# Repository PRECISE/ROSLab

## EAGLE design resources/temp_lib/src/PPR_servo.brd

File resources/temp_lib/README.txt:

The Blocks folder contains a number of known-good schematics.  

Until a automated ulp is created, the instructions for making a new board are as follows:
1. Make a new schematic: File>New>Schematic
2. Import schematics: File>Import> find the schematic files you want included
	a) The only nets that should be connected by default (old name = new name) are V+, +5V, +3V3, GND or any other power rails or busses
3. Eagle does not carry over the sheet descriptions when imported.  Open the original files, right click on the sheet, select description, copy the html code.  
	a) Repeat the above steps in the new, combined schematic file, and paste the description in the appropriate location.
4. Read the instructions in the description.  It should instruct you to connect pins and anything else required for the circuit.  Look out for optional components.
	a) To connect pins, draw nets that are connected to the pins (they may already exist).  Do the same for all connected pins.  Then, rename all nets that should be connected to the same name.
5. Your schematic should be done at this point.  It is time to create a board from the schematic.
	a) To make a board from a schematic, File>Switch to Board> select yes if it asks to create from schematic.

Making new blocks:
1. Make a single sheet schematic
2. Add and connect symbols until you have a well contained part
3. For all nets that interact with outside schematic sheets, place a BLOCK_CONNECTOR symbol for each net and connect them
4. Name the nets according to the naming convention below:
	a) Serivce,Service#,1-to-many-symbol,Input-output-symbol,SuperService,SuperService#,AlternateFunction#/ ... (repeat for all possible services).PORT,PININ
	b) service (super service) options: GPIO (#), PWM (TIMER), PWM_N (TIMER), QEP (TIMER), TXRX (UART), SCK (SPI), MISO (SPI), MOSI (SPI), SCL (I2C), SDA (I2C), D+ (USB), D- (USB)

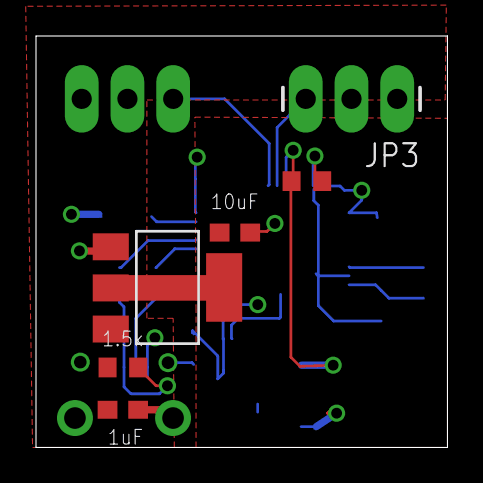
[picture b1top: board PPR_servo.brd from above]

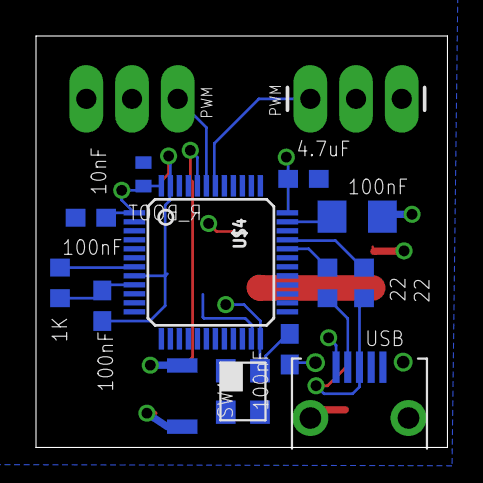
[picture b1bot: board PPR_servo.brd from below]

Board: 2 copper layers, 22.9 x 22.9 mm, 20 parts (14 on the bottom side), 13 nets.

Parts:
C6: 10 nF; C0402
CN2: USB-RECEPTABLE; FCI-10103594-0001LF
C_BYP_IN_1: 100nF; C1206
C_BYP_OUT_1: 10µF; C0603
C_MC_VDDA_1: 100nF; C0603
C_MC_VDD_1_1: 4.7uF; C0603
C_MC_VDD_2_1, C_MC_VDD_3_1: 100nF; C0603
C_USB_DC1: 1µF; C0603
JP1, JP3: 1X03_LONGPADS
R1, R3: 22; R0603
R2: 1.5k; R0603
R_BOOT_PU_1: 1k; R0603
R_NRST_PU_1: 1k; R0603
SW1: B3U
U$4: STM32F303CX; LQFP48
U$48: REG_SOT223LD1117XX; SOT-223
U$54: ASTX-H11

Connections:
3_3V,+,1: C6.1, C_BYP_OUT_1.1, C_MC_VDD_1_1.1, C_MC_VDD_2_1.1, C_MC_VDD_3_1.1, SW1.P$2, U$4.1, U$4.24, U$4.36, U$4.48, U$48.2, U$48.4, U$54.P$4
3_3V,+,I: C_MC_VDDA_1.1, R_NRST_PU_1.1, U$4.9
5V_USB,+,1: CN2.1, C_BYP_IN_1.1, C_USB_DC1.1, JP1.2, JP3.2, R2.1, U$48.3
16MHZ_CMOS,#,+,O,OSCILLATOR: U$4.5, U$54.P$3
BOOT0_1: R_BOOT_PU_1.1, SW1.P$1, U$4.44
D+,-,USB,1: R1.2, U$4.33
D+_IN_1: CN2.3, R1.1, R2.2
D-,-,USB,1: R3.2, U$4.32
D-_IN_1: CN2.2, R3.1
GND: C6.2, CN2.5, CN2.P$1, CN2.P$2, CN2.P$3, CN2.P$4, C_BYP_IN_1.2, C_BYP_OUT_1.2, C_MC_VDDA_1.2, C_MC_VDD_1_1.2, C_MC_VDD_2_1.2, C_MC_VDD_3_1.2, C_USB_DC1.2, JP1.1, JP3.1, R_BOOT_PU_1.2, U$4.8, U$4.23, U$4.35, U$4.47, U$48.1, U$54.P$2
NRST_1: R_NRST_PU_1.2, U$4.7
TIMER,PWM,-,1: JP1.3, U$4.42
TIMER,PWM,-,2: JP3.3, U$4.43

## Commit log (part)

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2014-02-26 Create gh-pages branch via GitHub
2014-02-26 Initial import from existing 'roslab' repo.
2014-02-26 Initial JavaFX project skeleton.
2014-02-26 Adding referenced libraries.
2014-03-10 Added base module set.
2014-03-10 Added loading of built-in modules from file.
2014-03-10 Removed unused include.
2014-03-10 Added release directory.
2014-03-10 Updated FXML file.
2014-03-12 Organized files into v1 release.
2014-03-12 Renamed version to v1.0.0.
2014-03-18 Added example entry to modules.xml.
2014-03-18 Added README: user documentation.
2014-03-18 New v1.0.0 archive with recent changes included.
2014-03-27 Renamed Channel class to Link.
2014-03-27 Adding new classes.
2014-03-27 Added new classes.
2014-03-27 Renamed these classes.
2014-03-27 Updated root type. Added application window title.
2014-03-27 Removed unused css file.
2014-03-27 Added TreeView.
2014-03-27 Updated constructors.
2014-04-08 Removed default status label text.
2014-04-08 Building data model classes.
2014-04-23 Added quad templates.
2014-05-13 Added JDOM and String Template libraries.
2014-05-13 Added ROS templates.
2014-05-13 Added Model Processor stub classes.
2014-05-16 Added new hardware model classes.
2014-05-16 Added getters/setters.
2014-05-16 Added HW Bot template.
2014-05-16 Updated HWBlockTypes.
2014-05-19 Added test for HardwareModelProcessor.
2014-05-19 Added getName() method to Endpoint interface.
2014-05-19 Changed Link name to be based on names of src and dest.
2014-05-19 Added getUILinksOfType() method to Configuration.
2014-05-19 Added string building for all HardwareModelProcessor methods.
2014-05-22 Python project files added due to use of Python in generated output files.
2014-05-22 Added main launch file for ROSLab FX.
2014-05-22 Changed str.concat to str +=
2014-05-22 Added fx:id for tab panes.
2014-05-22 Added FXML tags on tab panes.
2014-05-22 Added methods to Pin.
2014-05-22 Added constructors to PinService.
2014-05-22 Added more complete test configuration.
2014-05-22 Increased UINode size and changed color.
2014-05-22 Added CSS styling.
2014-05-23 Seems to have fixed scroll bars showing in ScrollPane.
2014-05-23 Added selection rectangle to ROSLabController.
2014-05-26 Removed PyDev from project.
2014-05-29 Added UIEndpoints to UINodes.
    Draggable with the UINode, too!
2014-06-05 Designing Dialog window for adding links.
2014-06-05 Adding support for drawing links in the UI.
2014-06-05 Adjusted node stroke colors.
2014-06-05 Added test nodes to other tab panes.
2014-07-21 Work on TreePane
2014-07-21 Updated project-specific Eclipse settings.
2014-07-21 Updated project-specific properties.
2014-07-22 Added ability to modify User Defined Node ports.
2014-07-31 Added getNodesOfClass method.
2014-07-31 Work on modifying ROSNodes for testing.
2014-09-11 Code formatting cleanup.
2014-09-11 Changed Node class to not use JavaFX properties (for now).
2014-09-11 Added addJoint method to HWBlock class.
2014-09-11 Added some basic getter/setter methods for main model classes.
2014-10-03 Added XStream library.
2014-10-06 Formatting update.
2014-10-06 Fixed Library tree loading.
2014-10-07 Added fxml for Functionality window.
2014-10-08 Updated formatting.
2014-10-14 Added JavaFX handles for tabs.
2014-10-14 Minor method name tweak.
2014-10-14 Added mouse event handling.
2014-10-14 Added UINode and UILink handling methods.
2014-10-14 Added SnakeYAML and Jython libraries to project.
2014-10-14 Added Mechanics Python-handling code from PPR branch.
2014-10-14 Changed field visibility to protected.
2014-10-20 Moved processor classes.
2014-10-27 Added unimplemented methods.
2014-10-27 Added scroll panes to right-hand-side accordion.
    Updated tab names slightly.
2014-10-27 Added ROSModelCompiler class from ROSLab 1.0
2014-10-27 Updated import.
2014-11-18 Added rosmsgs.
2014-11-18 Added null checks.
2014-11-18 Added another ROSPortType: Odometry.
2014-11-18 Added example ROS package.
2014-11-19 Switched to use StringTemplate 3.2.1.
2014-11-19 Renamed ROSModelCompiler.
2014-11-19 Updated ROS template files.
2014-11-19 Fixed whitespace in templates.
2014-11-19 Added new constructors for Circuit, Joint, HWBlock.
2014-11-19 Moved HardwareModelProcessorTest.
2014-11-19 Improved constructors.
2014-11-19 Added rate methods and publishers/subscribers methods.
2014-11-20 Added Platform class, a test class for the parser, and a test Platform YAML file.
2014-11-21 Added electronics schematics, moved mechanics and software libraries.
2014-11-21 Added ROSPortType class with static map of ROS message types.
2014-11-24 Finished Platform and PlatformParser.
2014-11-24 Commented out blocks to be updated later for version 2 data model.
2014-11-26 Cleanup.
2014-11-26 Added ROSTopic class.
2014-11-26 Updated author.
2014-12-09 Improved Link API.
2014-12-09 Added Platform feature.
2014-12-09 Added some helper functions.
2014-12-09 Added new dialog windows.
2014-12-16 Excluding a couple of unused classes.
2014-12-16 Deleted unused package-info classes.
2014-12-16 Added EagleSchematic class to handle interactions with EAGLE schematics.
2014-12-16 Added clone support to main model classes.
    Also, added electronics naming scheme parsing.
2014-12-17 Added NewNodeDialog and fixed other dialogs.
2014-12-17 Added name field to Library.
2014-12-17 Added contains() methods and getEndpoints() to Configuration class.
2014-12-17 Removed obsolete class.
2014-12-17 Added context menu support to tree.
2014-12-17 Switched Configuration back to using non-UI-specific classes.
2014-12-18 Added remove methods.
2014-12-18 Updated test to use non-UI classes.
2014-12-18 Added back non-UI getLinksOfType method.
2014-12-19 Reorganized UI package structures.
2014-12-19 Added getNodesOfType(clazz) method.
2014-12-20 Removed obsolete commented code.
2014-12-20 Added NewUserDefinedDialog.
2014-12-20 Made ROSMsgType class comparable.
2014-12-20 Removed obsolete and duplicate code from ROSLabTree class, added some removal methods.
2014-12-20 Improved Library & Configuration add and remove methods.
2014-12-20 Suppressing 'unchecked' warnings in PythonLibraryHelper.
2014-12-20 Updated fxbuild file, ignoring build directory for Git.
2014-12-20 Removed obsolete ROSLabTreeCell code, copied drag method to ROSLabTree class for future use.
2014-12-22 Added isInput and getAnnotations methods to Endpoints.
2014-12-22 Added FXML annotations to methods in ROSLabController.
    Added additional menu items to File menu.
2014-12-22 Added suppress warnings to dialog classes.
2014-12-23 Added TODO to ROSMsgType class.
2014-12-23 Improved topic info shown under Library nodes.
2014-12-23 Using Landshark platform library.
2015-01-13 Added switchLibrary method stub.
2015-01-13 Added loading of Electronics library.
    Includes methods for creating Circuit objects from EagleSchematics.
2015-01-13 Added eagle.dtd.
2015-01-14 Improved schematic parsing and creation of Pin objects.
2015-01-14 Fixed issues in schematic Net names.
2015-01-14 Added "simple" versions of two schematics.
2015-01-14 Swapped source and destination pins when attempting a connection.
2015-01-15 Fixed pin connection check, fixed missing assignedService assignment.
2015-01-24 Added getUIEndpoint method.
2015-01-24 Added ability to set UINode text, removed duplicated UINode text for Circuit blocks.
2015-01-24 Added check to ensure NewLinkDialog does not allow self-connections.
2015-01-25 Added check to ensure name field in NewNodeDialog is not empty.
2015-01-25 Added 'net' String field to Pin.
2015-03-02 Added Z3 library.
2015-03-02 Added pin matching algorithm.
2015-03-04 Added slf4j library.
2015-03-05 Added log4j.
2015-03-09 Added 'Delete' context menu item for the Links.
2015-03-11 Fixed typo in indexing.
2015-03-11 Added extra methods to Endpoint class.
2015-03-11 Added destroy() method to Link.
2015-03-12 Added link removal improvements, fixed indexing bugs in PinMatcher.
2015-03-12 Simplified Ok handler for NewLinkDialog.
2015-03-12 Fixed merge method for schematics, integrated pin-matching algorithm into Circuit connection process.
2015-03-13 Added more schematics.
2015-03-19 Simplified some schematic blocks.
2015-03-19 Attempting to display UILink in the background.
2015-03-19 Working towards fixing library and package merging issue.
2015-03-20 Fixed error in DeviceSet list iteration.
2015-03-22 Added random testing to PinMatcherTest.
2015-03-22 Trying to fix Z ordering of UILinks.
2015-03-22 Fixed Circuit so wire bundles are added to both Src and Dest when making a connection.
2015-03-22 Removing optional service from Radio pin.
2015-03-24 Added more checks to Pin connect().
2015-03-30 Adjusted pin matching algorithm to check for bus connections and to finish even when not fully connected
2015-03-30 Added parsing of destination set value on pin names
2015-03-31 Added new basic PinService constructor.
2015-03-31 Updated constructor to support bidirectionality.
2015-03-31 Fixed bug in bussable check in PinMatcher.
2015-03-31 Updated NewLinkDialog to disable Destination box when there aren't any valid destinations.
2015-03-31 Disabled superservice checking, improved I/O matching.
2015-04-06 Changed Standard Servo Header pin to Required.
2015-04-06 Added battery schematics.
2015-04-06 Fixed bug in pin name parsing, improved Wire naming.
2015-04-06 Updated driver schematic.
2015-04-06 Updated IMU schematic.
2015-04-06 Updated merge output to be saved in separate folder.
2015-04-06 Handle showing when Required pins are unconnected before generating merged output.
2015-04-18 Adjusted UINode text layout.
2015-04-19 Changed schematics to pick an assigned service.
2015-04-20 Drag and drop ports
2015-04-20 Changed UIEndpoint from Group to Circle.
2015-05-08 Changed to Triple Tree Mode!
2015-05-19 Added TODO
2015-05-19 Updated Electronics Block Library.
2015-05-19 Added new electronics blocks.
2015-05-19 Fixed recursion error in UINode class.
2015-05-19 Fixed typo in Oscillator block.
2015-05-21 Updated voltage setting in Regulator.
2015-06-02 Separated custom ROSNode menus
2015-06-02 Can change rate on controller node
2015-06-03 Load library dialog for SW
2015-06-04 Added electronics naming scheme document.
2015-06-04 Added support for loading and saving configuration dialogs.
2015-06-04 Modified motor schematic to make LOAD not busable, added sample verification YAML file.
2015-06-05 Add node on all tabs, fixed ROSPort canConnect, tab order on forms
2015-07-01 Code gen checks for links on port
2015-07-07 Rm ROSPort fan check, added port name checks
2015-07-16 Changed PlatformParser to LibraryParser and added functionality.
2015-07-18 Completed ConfigurationParser and test.
2015-07-19 Added a Z3 class to be used for verification steps.
2015-07-20 Adding battery verification files.
2015-07-20 Adding more blocks: Sparkfun Li-Po 400mah, 850mah, and ITG3701 gyros
2015-07-20 Added a couple of new verification types.
2015-07-31 Added right-click Delete menus for Nodes on canvas and tree.
2015-07-31 Improved removing of Config Nodes.
2015-07-31 Use iterators for remove actions.
2015-08-02 Minor changes to PinMatcher files.
2015-08-02 Removed obsolete temp lib folder.
2015-08-02 Removed unused libraries.
2015-08-03 Made some 'Save' menu items invisible.
2015-08-03 Changed node_type names in Library YAML.
2015-08-05 Updated node_type fields in test Library YAML files, added format field to YAML files, added YAML validity methods.
2015-08-05 Adjusted divider position for tabs.
2015-08-05 Added format YAML element to be included when emitting Library and Configuration YAML.
2015-08-27 Merged in Brad's code.
    SW ScrollPane and ROSNodeCodeGenerator alerts.
2021-05-14 Bump junit from 4.10 to 4.13.1 in /lib/slf4j-1.7.10
    Bumps [junit](https://github.com/junit-team/junit4) from 4.10 to 4.13.1.
    - [Release notes](https://github.com/junit-team/junit4/releases)
    - [Changelog](https://github.com/junit-team/junit4/blob/main/doc/ReleaseNotes4.10.md)
    - [Commits](https://github.com/junit-team/junit4/compare/r4.10...r4.13.1)

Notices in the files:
parts and their libraries:
SparkFun: Licensing: CC v3.0 Share-Alike You are welcome to use this library for commercial purposes.
